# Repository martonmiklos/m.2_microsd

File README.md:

## What?

M.2 E keyed adapter card for micro SD socket drawn in Kicad 7

Designed for a Wyse 3040 thin client.

Inspiration [coming from here](https://www.parkytowers.me.uk/thin/wyse/3040/storage.shtml)

#### Technology

Stackup: JLC04081H-7628 (0.8 mm 4 layers)

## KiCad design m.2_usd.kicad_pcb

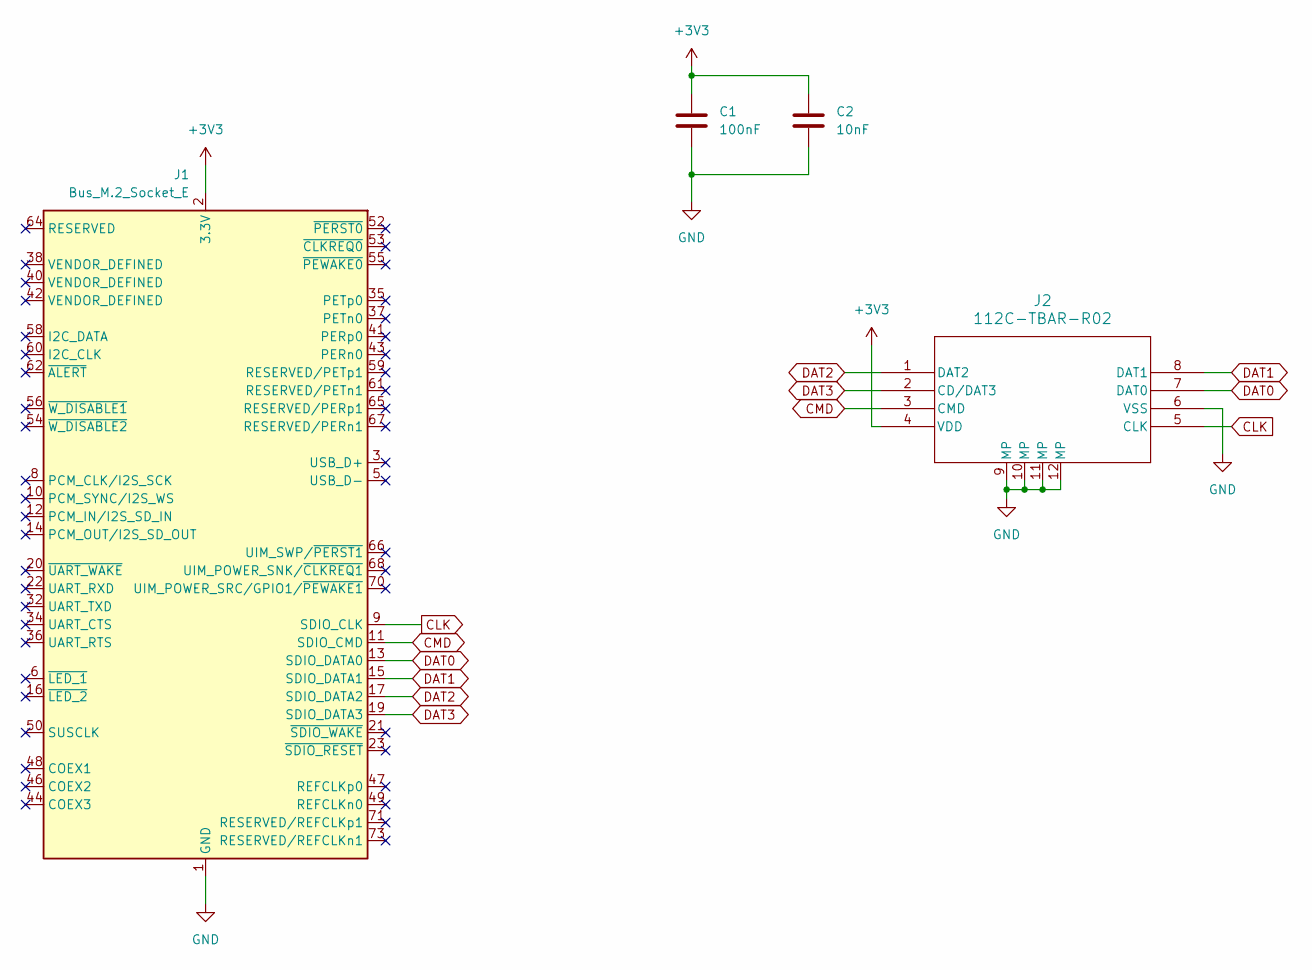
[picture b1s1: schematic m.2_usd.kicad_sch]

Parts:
C1: 100nF; C_0603_1608Metric
C2: 10nF; C_0603_1608Metric
J1: Bus_M.2_Socket_E; m2-padKeyE-2230
J2: 112C-TBAR-R02; 112C-TBAR-R02_ATT

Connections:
+3V3: C1.1, C2.1, J1.2 (3.3V), J1.4 (3.3V), J1.72 (3.3V), J1.74 (3.3V), J2.4 (VDD)
CLK: J1.9 (SDIO_CLK), J2.5 (CLK)
CMD: J1.11 (SDIO_CMD), J2.3 (CMD)
DAT0: J1.13 (SDIO_DATA0), J2.7 (DAT0)
DAT1: J1.15 (SDIO_DATA1), J2.8 (DAT1)
DAT2: J1.17 (SDIO_DATA2), J2.1 (DAT2)
DAT3: J1.19 (SDIO_DATA3), J2.2 (CD/DAT3)
GND: C1.2, C2.2, J1.1 (GND), J1.7 (GND), J1.18 (GND), J1.33 (GND), J1.39 (GND), J1.45 (GND), J1.51 (GND), J1.57 (GND), J1.63 (GND), J1.69 (GND), J1.75 (GND), J2.6 (VSS), J2.9 (MP), J2.10 (MP), J2.11 (MP), J2.12 (MP)

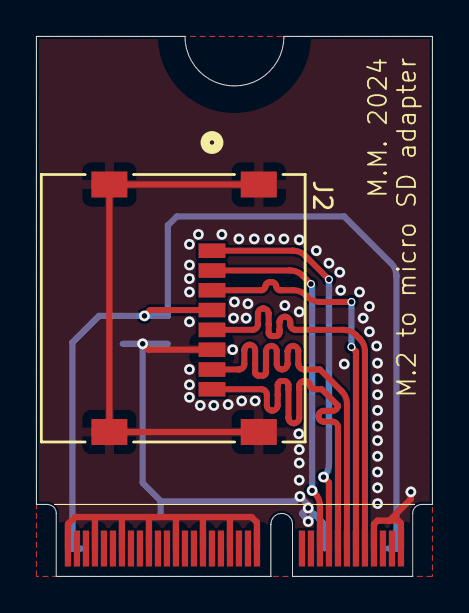
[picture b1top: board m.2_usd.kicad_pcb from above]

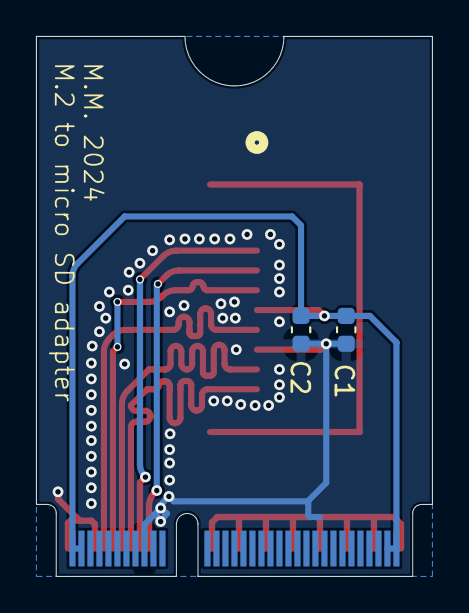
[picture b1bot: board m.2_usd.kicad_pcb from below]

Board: 4 copper layers, 22.0 x 30.0 mm, 4 parts (2 on the bottom side), 8 nets.

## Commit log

2024-05-19 Repo init before fixing Gabor's review comments
2024-05-19 Added extensive via stitching
2024-05-19 Polished silkscreen, added README.md
2024-05-19 ERC and DRC pass
2024-05-19 Update image
